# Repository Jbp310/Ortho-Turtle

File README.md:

# Ortho-Turtle

Ortho-Turtle is an ortholinear keyboard designed by me,  Fastturtle, for Hackclub's KEEB project.

**If you want to make this yourself, just grab the files from Production-Ready_Files, and you should be good to go.** 

# Design Philosophies:

Keyboard Layout:
I went for a fairly unique layout with this keyboard, as not only is it a ortholinear layout, but it's a fairly nonstandard amount of keys (81). My main motivator behind choosing the keys was having all the keys that I usually use, plus the ones that I would require to navigate an environment without a mouse, as I frequent janky linux distros.

PCB:
I designed my keyboard PCB fairly basically, as it's the first circuit board I've ever designed. I chose to use surface mount diodes, to give the keyboard a cleaner look, and to challenge my soldering skills a bit. Other than that though it's not particularly unique, although I'm quite happy with the design, especially with it being the first one I've made.

Case:
I chose to 3d print the case so that I could have more options when it comes to customizing it, additionally, it saves a lot of cost, as I'm able to use materials I have on hand, vs having to utilize grant funds. As for the actual case design I made a nice and simple tray mount, with a plate, to make it easier to 3d print. I plan on O-ring mounting the PCB to ensure a nicer, and more consistent typing experience.

# Things I learned:

I think the main lesson I learned throughout the development of this project was the importance of having a concrete idea of what you want before you start. As I could have saved a fair bit of time spent redesigning if I had just decided upon an idea to begin with. In addtition I also learned how to utilize KiCad.

# Credits

First of all, lots of thanks to Miles and the amazing team at Hackclub that helped put KEEB together, because without KEEB this project never would have been possible.

Secondly, thank you to Scotto Keebs for all the amazing guides on making custom keyboards.

Finally, me, I did design this whole keyboard, so you know, don't steal it, if have issues or questions just let me know, I'm always happy to help!

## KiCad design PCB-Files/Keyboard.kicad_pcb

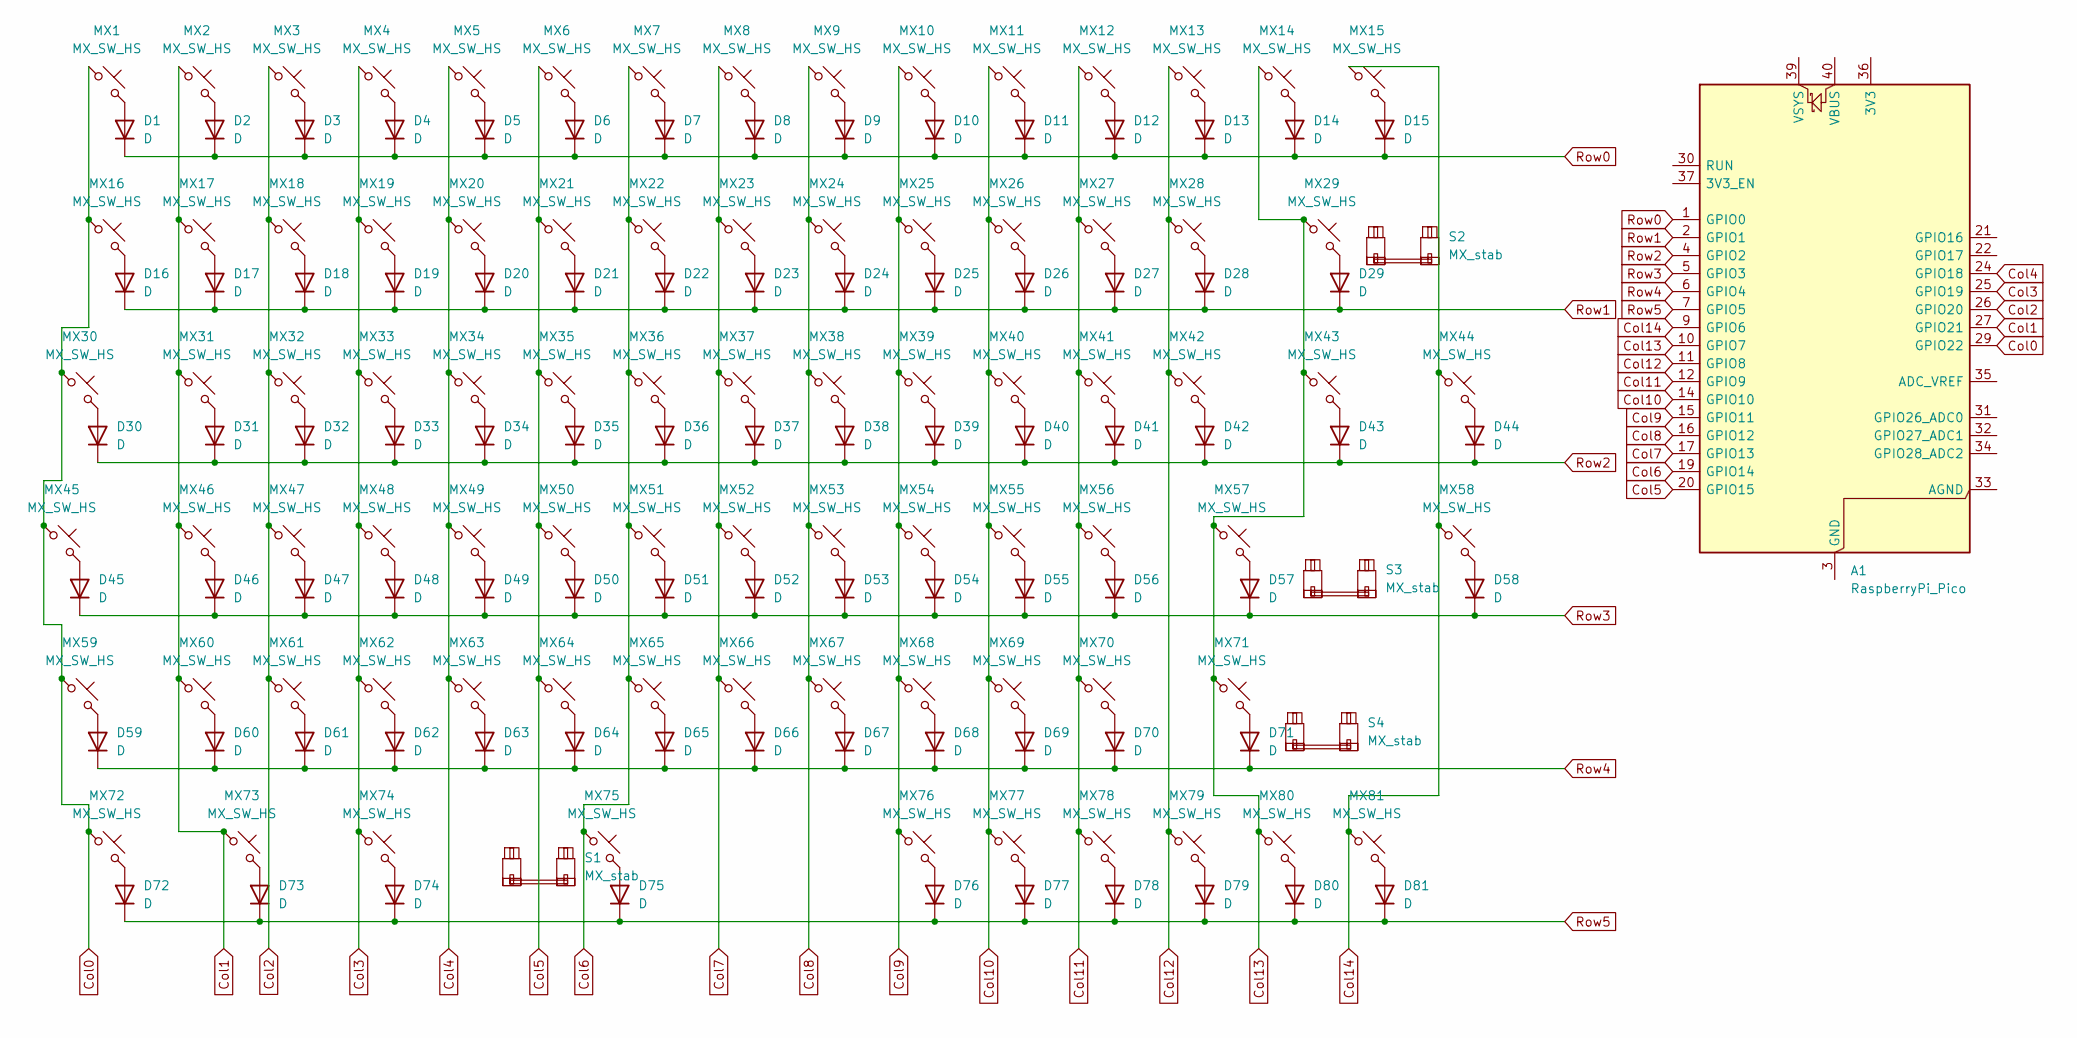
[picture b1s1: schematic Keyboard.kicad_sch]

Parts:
A1: RaspberryPi_Pico; RaspberryPi_Pico_Common_Unspecified
D1, D2, D3, D4, D5, D6, D7, D8, D9, D10, D11, D12, D13, D14, D15, D16, D17, D18, D19, D20, D21, D22, D23, D24, D25, D26, D27, D28, D29, D30, D31, D32, D33, D34, D35, D36, D37, D38, D39, D40, D41, D42, D43, D44, D45, D46, D47, D48, D49, D50, D51, D52, D53, D54, D55, D56, D57, D58, D59, D60, D61, D62, D63, D64, D65, D66, D67, D68, D69, D70, D71, D72, D73, D74, D75, D76, D77, D78, D79, D80, D81: D; D_SOD-123
MX1, MX2, MX3, MX4, MX5, MX6, MX7, MX8, MX9, MX10, MX11, MX12, MX13, MX14, MX15, MX16, MX17, MX18, MX19, MX20, MX21, MX22, MX23, MX24, MX25, MX26, MX27, MX28, MX29, MX30, MX31, MX32, MX33, MX34, MX35, MX36, MX37, MX38, MX39, MX40, MX41, MX42, MX43, MX44, MX45, MX46, MX47, MX48, MX49, MX50, MX51, MX52, MX53, MX54, MX55, MX56, MX57, MX58, MX59, MX60, MX61, MX62, MX63, MX64, MX65, MX66, MX67, MX68, MX69, MX70, MX71, MX72, MX73, MX74, MX75, MX76, MX77, MX78, MX79, MX80, MX81: MX_SW_HS; SW_MX_HS_CPG151101S11_1u
S1: MX_stab; STAB_MX_P_6.25u
S2: MX_stab; STAB_MX_P_2u
S3, S4: MX_stab; STAB_MX_P_2.25u

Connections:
Col0: A1.29 (GPIO22), MX1.1, MX16.1, MX30.1, MX45.1, MX59.1, MX72.1
Col1: A1.27 (GPIO21), MX2.1, MX17.1, MX31.1, MX46.1, MX60.1, MX73.1
Col2: A1.26 (GPIO20), MX3.1, MX18.1, MX32.1, MX47.1, MX61.1
Col3: A1.25 (GPIO19), MX4.1, MX19.1, MX33.1, MX48.1, MX62.1, MX74.1
Col4: A1.24 (GPIO18), MX5.1, MX20.1, MX34.1, MX49.1, MX63.1
Col5: A1.20 (GPIO15), MX6.1, MX21.1, MX35.1, MX50.1, MX64.1
Col6: A1.19 (GPIO14), MX7.1, MX22.1, MX36.1, MX51.1, MX65.1, MX75.1
Col7: A1.17 (GPIO13), MX8.1, MX23.1, MX37.1, MX52.1, MX66.1
Col8: A1.16 (GPIO12), MX9.1, MX24.1, MX38.1, MX53.1, MX67.1
Col9: A1.15 (GPIO11), MX10.1, MX25.1, MX39.1, MX54.1, MX68.1, MX76.1
Col10: A1.14 (GPIO10), MX11.1, MX26.1, MX40.1, MX55.1, MX69.1, MX77.1
Col11: A1.12 (GPIO9), MX12.1, MX27.1, MX41.1, MX56.1, MX70.1, MX78.1
Col12: A1.11 (GPIO8), MX13.1, MX28.1, MX42.1, MX79.1
Col13: A1.10 (GPIO7), MX14.1, MX29.1, MX43.1, MX57.1, MX71.1, MX80.1
Col14: A1.9 (GPIO6), MX15.1, MX44.1, MX58.1, MX81.1
unnamed: A1.3 (GND), A1.8 (GND), A1.13 (GND), A1.18 (GND), A1.23 (GND), A1.28 (GND), A1.38 (GND)
unnamed: D1.2 (A), MX1.2
unnamed: D2.2 (A), MX2.2
unnamed: D3.2 (A), MX3.2
unnamed: D4.2 (A), MX4.2
unnamed: D5.2 (A), MX5.2
unnamed: D6.2 (A), MX6.2
unnamed: D7.2 (A), MX7.2
unnamed: D8.2 (A), MX8.2
unnamed: D9.2 (A), MX9.2
unnamed: D10.2 (A), MX10.2
unnamed: D11.2 (A), MX11.2
unnamed: D12.2 (A), MX12.2
unnamed: D13.2 (A), MX13.2
unnamed: D14.2 (A), MX14.2
unnamed: D15.2 (A), MX15.2
unnamed: D16.2 (A), MX16.2
unnamed: D17.2 (A), MX17.2
unnamed: D18.2 (A), MX18.2
unnamed: D19.2 (A), MX19.2
unnamed: D20.2 (A), MX20.2
unnamed: D21.2 (A), MX21.2
unnamed: D22.2 (A), MX22.2
unnamed: D23.2 (A), MX23.2
unnamed: D24.2 (A), MX24.2
unnamed: D25.2 (A), MX25.2
unnamed: D26.2 (A), MX26.2
unnamed: D27.2 (A), MX27.2
unnamed: D28.2 (A), MX28.2
unnamed: D29.2 (A), MX29.2
unnamed: D30.2 (A), MX30.2
unnamed: D31.2 (A), MX31.2
unnamed: D32.2 (A), MX32.2
unnamed: D33.2 (A), MX33.2
unnamed: D34.2 (A), MX34.2
unnamed: D35.2 (A), MX35.2
unnamed: D36.2 (A), MX36.2
unnamed: D37.2 (A), MX37.2
unnamed: D38.2 (A), MX38.2
unnamed: D39.2 (A), MX39.2
unnamed: D40.2 (A), MX40.2
unnamed: D41.2 (A), MX41.2
unnamed: D42.2 (A), MX42.2
unnamed: D43.2 (A), MX43.2
unnamed: D44.2 (A), MX44.2
unnamed: D45.2 (A), MX45.2
unnamed: D46.2 (A), MX46.2
unnamed: D47.2 (A), MX47.2
unnamed: D48.2 (A), MX48.2
unnamed: D49.2 (A), MX49.2
unnamed: D50.2 (A), MX50.2
unnamed: D51.2 (A), MX51.2
unnamed: D52.2 (A), MX52.2
unnamed: D53.2 (A), MX53.2
unnamed: D54.2 (A), MX54.2
unnamed: D55.2 (A), MX55.2
unnamed: D56.2 (A), MX56.2
unnamed: D57.2 (A), MX57.2
unnamed: D58.2 (A), MX58.2
unnamed: D59.2 (A), MX59.2
unnamed: D60.2 (A), MX60.2
unnamed: D61.2 (A), MX61.2
unnamed: D62.2 (A), MX62.2
unnamed: D63.2 (A), MX63.2
unnamed: D64.2 (A), MX64.2
unnamed: D65.2 (A), MX65.2
unnamed: D66.2 (A), MX66.2
unnamed: D67.2 (A), MX67.2
unnamed: D68.2 (A), MX68.2
unnamed: D69.2 (A), MX69.2
unnamed: D70.2 (A), MX70.2
unnamed: D71.2 (A), MX71.2
unnamed: D72.2 (A), MX72.2
unnamed: D73.2 (A), MX73.2
unnamed: D74.2 (A), MX74.2
unnamed: D75.2 (A), MX75.2
unnamed: D76.2 (A), MX76.2
unnamed: D77.2 (A), MX77.2
unnamed: D78.2 (A), MX78.2
unnamed: D79.2 (A), MX79.2
unnamed: D80.2 (A), MX80.2
unnamed: D81.2 (A), MX81.2
Row0: A1.1 (GPIO0), D1.1 (K), D2.1 (K), D3.1 (K), D4.1 (K), D5.1 (K), D6.1 (K), D7.1 (K), D8.1 (K), D9.1 (K), D10.1 (K), D11.1 (K), D12.1 (K), D13.1 (K), D14.1 (K), D15.1 (K)
Row1: A1.2 (GPIO1), D16.1 (K), D17.1 (K), D18.1 (K), D19.1 (K), D20.1 (K), D21.1 (K), D22.1 (K), D23.1 (K), D24.1 (K), D25.1 (K), D26.1 (K), D27.1 (K), D28.1 (K), D29.1 (K)
Row2: A1.4 (GPIO2), D30.1 (K), D31.1 (K), D32.1 (K), D33.1 (K), D34.1 (K), D35.1 (K), D36.1 (K), D37.1 (K), D38.1 (K), D39.1 (K), D40.1 (K), D41.1 (K), D42.1 (K), D43.1 (K), D44.1 (K)
Row3: A1.5 (GPIO3), D45.1 (K), D46.1 (K), D47.1 (K), D48.1 (K), D49.1 (K), D50.1 (K), D51.1 (K), D52.1 (K), D53.1 (K), D54.1 (K), D55.1 (K), D56.1 (K), D57.1 (K), D58.1 (K)
Row4: A1.6 (GPIO4), D59.1 (K), D60.1 (K), D61.1 (K), D62.1 (K), D63.1 (K), D64.1 (K), D65.1 (K), D66.1 (K), D67.1 (K), D68.1 (K), D69.1 (K), D70.1 (K), D71.1 (K)
Row5: A1.7 (GPIO5), D72.1 (K), D73.1 (K), D74.1 (K), D75.1 (K), D76.1 (K), D77.1 (K), D78.1 (K), D79.1 (K), D80.1 (K), D81.1 (K)

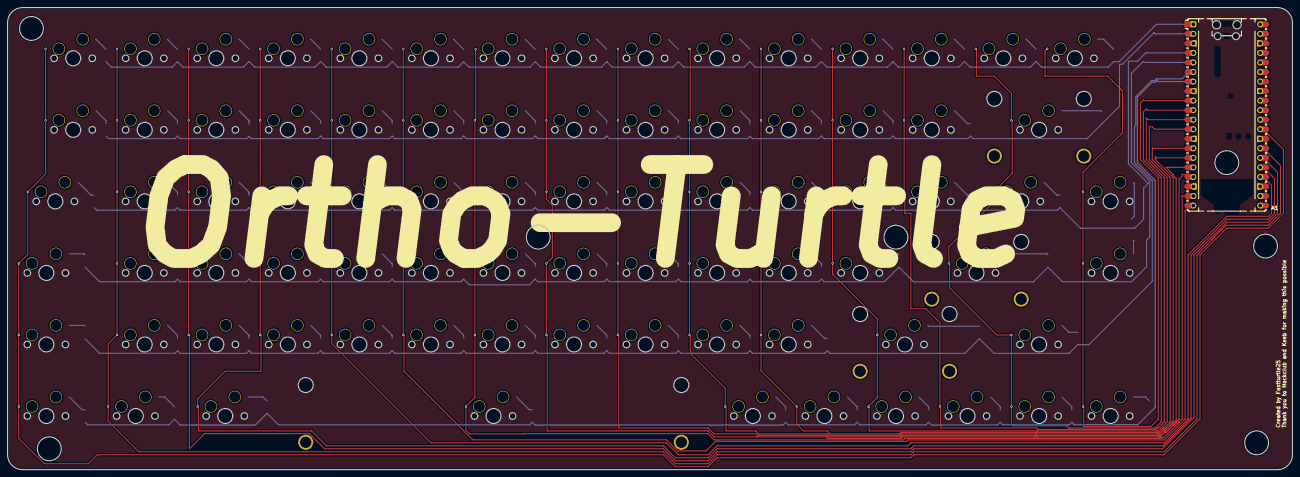
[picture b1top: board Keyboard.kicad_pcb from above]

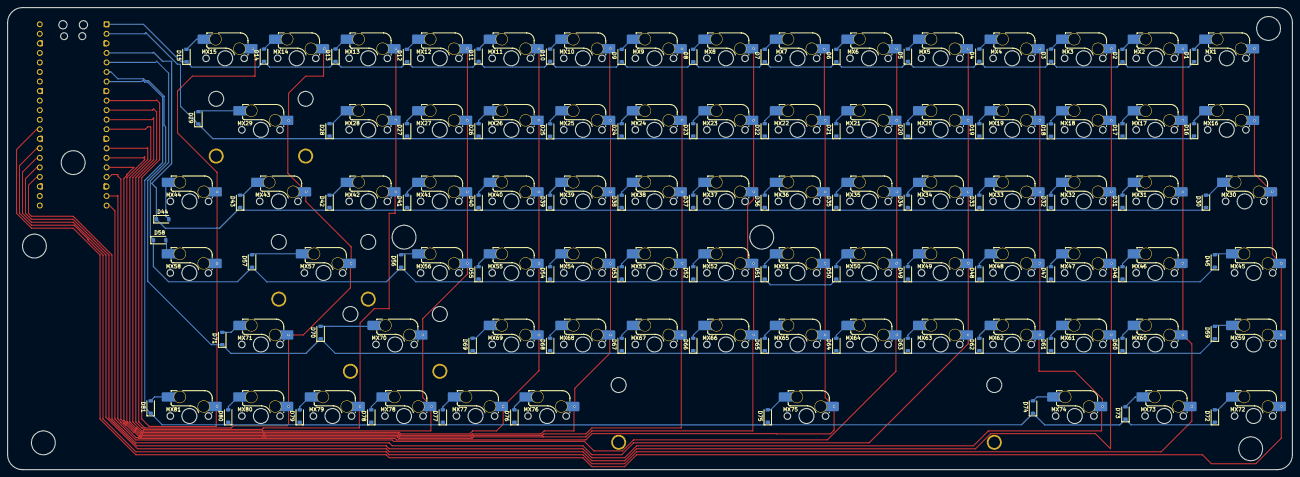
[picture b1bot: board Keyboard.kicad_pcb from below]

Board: 2 copper layers, 342.1 x 123.0 mm, 167 parts (162 on the bottom side), 103 nets.
